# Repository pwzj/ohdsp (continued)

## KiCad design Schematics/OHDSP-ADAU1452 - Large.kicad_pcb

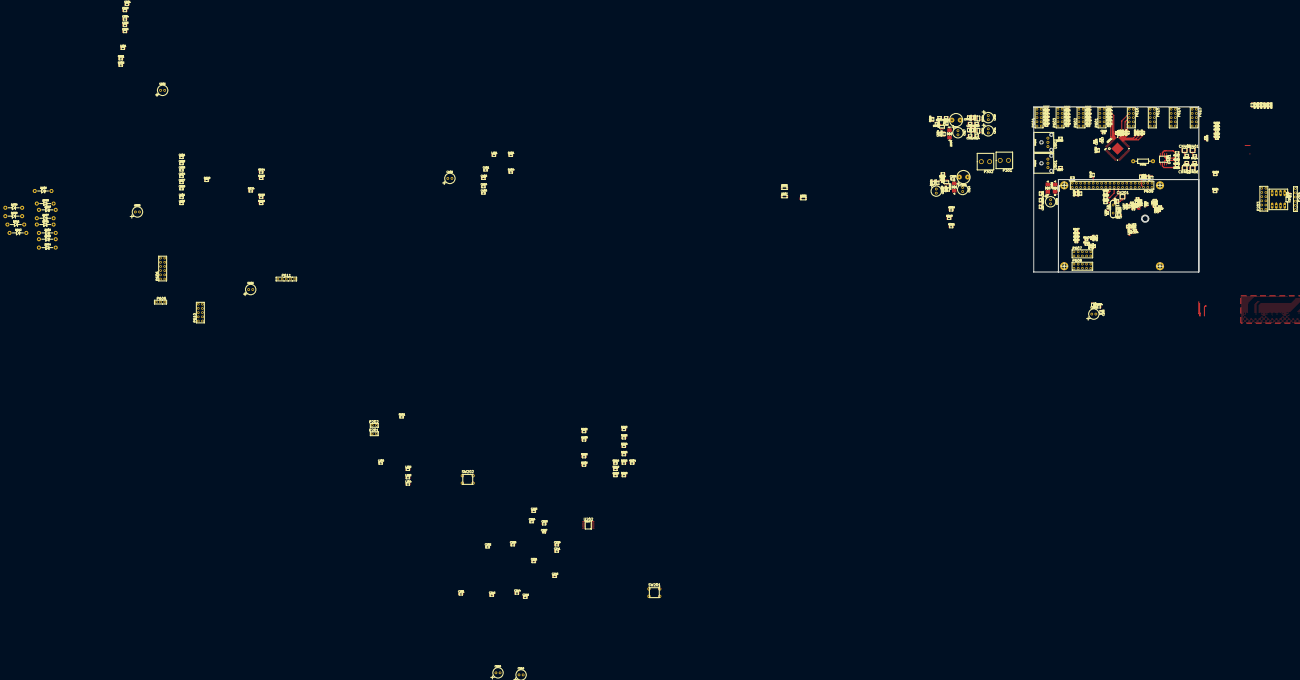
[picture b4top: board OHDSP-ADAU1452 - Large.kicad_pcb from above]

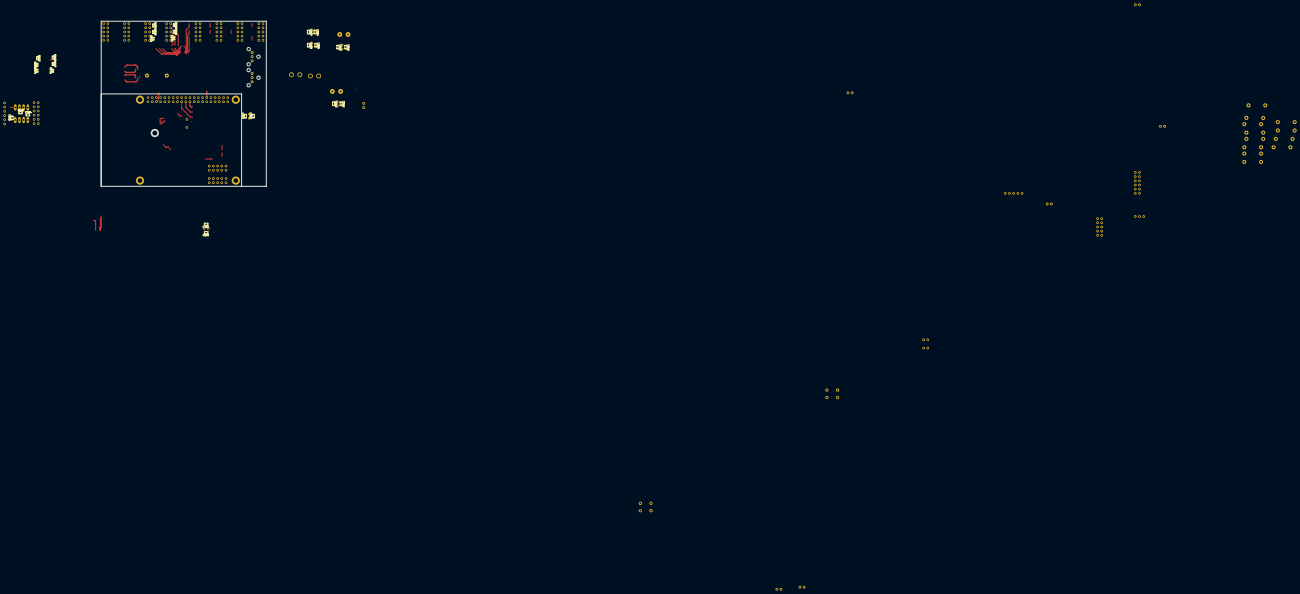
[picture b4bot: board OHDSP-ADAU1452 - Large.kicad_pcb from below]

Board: 2 copper layers, 100.0 x 100.0 mm, 305 parts (27 on the bottom side), 168 nets.

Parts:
C201, C202, C206, C218, C231, C252, C305, C306, C312, C316, C319, C328, C329, C334, C335, C404, C405, C504, C505, C506, C601, C602: 100n; SMD-0805
C203, C214, C224, C239, C245, C307, C401, C501, C607, C608: 100p; SMD-0805
C204, C240, C248, C301, C308, C314, C317, C402, C502, C605, C606: 220u; CAP-TH-D6.3mmP2.5mm
C205, C226, C241, C250, C303, C304, C311, C313, C315, C325, C326, C337, C338, C403, C503, C603, C604: 22u; SMD-0805
C207, C210, C213, C219, C228, C230, C233, C235: 1u; SMD-0603
C208, C211, C215, C220, C227, C229, C232, C234, C236, C242, C251: 100n; SMD-0603
C209, C212, C217, C223: 10n; SMD-0603
C216, C254, C321, C330: 1u; SMD-0805
C221: 5n6; SMD-0603
C222: 150p; SMD-0603
C225: 220u; SMD-0805
C237, C238: 33p; SMD-0603
C309, C310, C331, C507: 10n; SMD-0805
C340, C341: 100u; CAP-TH-D6.3mmP2.5mm
CN201, CN401, CN402, CN405, CN406: COAX; CONN-RF-UFL
D301, D302, D303, D304: SS24T3G; DIODE-SMB
D305, D306, D307: LED; SMD-1206
D601, D602, D603, D604, D605, D606, D607, D608, D609, D610, D611, D612: 1N5818; DIODE-DO-41
L201, L202, L203, L204, L205, L301, L401, L501, L601, L602: 600R@100MHz; SMD-0805
L302: 744772047; PASSIVE-TH-IND-WURTH-5mm
L303: 744772220; PASSIVE-TH-IND-WURTH-5mm
P201, P202: CONN_2x1; CONN_SIL_2
P203, P606: CONN_6X2; CONN_DIL_2X6
P204: CONN_6x1; CONN_SIL_6
P301, P302: CONN_2x1; CONN-SCREW-2WAY-5mm-5.08mm
P303, P304, P305, P306: PIN; MNT_HOLE_2.5mm
P601, P602, P603, P604, P607, P608, P610, P613, P614, P615, P616: CONN_02X05; CONN_DIL_2X5
P605: CONN_3x1; CONN_SIL_3
P609: CONN_02X20; CONN_DIL_2X20
P611: CONN_5x1; CONN_SIL_5
R201, R205, R404: 1k; SMD-0805
R202, R203: 2k2; SMD-0805
R204, R206, R225, R228, R234, R303, R401, R501, R648, R649: 47R; SMD-0805
R207, R208, R209, R210, R213, R214, R604, R605, R606, R607, R608, R609, R610, R611, R612, R613, R614, R615: 0R; SMD-0603
R211, R212, R215, R216, R616, R617, R618, R619, R620, R621, R622, R623, R624, R625, R626, R627, R662, R663, R664, R665, R666, R667, R668, R669, R670, R671, R672, R673: N/F; SMD-0603
R217: 4k3; SMD-0805
R218, R221, R308, R503, R628, R629, R630, R631, R632, R633, R634, R641, R643, R644, R645, R646, R647: 0R; SMD-0805
R219: 12k; SMD-0805
R220: 3k3; SMD-0805
R222, R229, R230, R414, R415, R418, R419, R601, R602, R603, R674: N/F; SMD-0805
R223: 3k; SMD-0805
R224: 3k6; SMD-0805
R226, R301, R302, R313: 100k; SMD-0805
R227: 100R; SMD-0805
R231, R232, R307, R314, R502: 10k; SMD-0805
R304: 47k; SMD-0805
R305: 97k6; SMD-0805
R306: 39k; SMD-0805
R309, R310, R311: 470R; SMD-0805
R402: 75R; TH-RES-0W25
R406, R407, R408, R409: 27R; SMD-0805
R635, R636, R637, R638, R639, R640: 4k7; SMD-0805
R650, R651, R652, R653, R654, R655, R656, R657, R658, R659, R660, R661: 27R; SMD-0603
SW201, SW202: SWITCH; SW_TACT_TH
U201: ADAU1452WBCPZ; IC-LFCSP72-HANDFIT
U202: ADM13307-5ARZ; IC_SOIC_8
U203: 25AA1024; IC_DIP_8
U301, U302: IC-REG-XRP7659ISTR-F; IC-SOT23-6
U304, U305: IC-REG-XC6210B332MR; IC-SOT25
U401: NB3L553; IC_SOIC_8
U501: IC-SPDIF-RX-OPTO; IC_SPDIF_OPTO
U502: IC-SPDIF-TX-OPTO; IC_SPDIF_OPTO
X201: 24M576; XTAL_HC49_TH

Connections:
+5V: D301.1, L602.1, P301.1, R641.2
/ADAU1452/ADAU_SPDIF_RX: C507.1, U201.4
/ADAU1452/ADAU_SPDIF_TX: R503.1, U201.5
/ADAU1452/ADCIN_BCLK0: R605.2, R620.2, U201.58
/ADAU1452/ADCIN_BCLK1: R608.2, R621.2, U201.61
/ADAU1452/ADCIN_BCLK2: R611.2, R622.2, U201.66
/ADAU1452/ADCIN_BCLK3: R602.2, R614.2, R623.2, U201.69
/ADAU1452/ADCIN_LRCLK0: R604.2, R624.2, U201.57
/ADAU1452/ADCIN_LRCLK1: R607.2, R625.2, U201.60
/ADAU1452/ADCIN_LRCLK2: R610.2, R626.2, U201.65
/ADAU1452/ADCIN_LRCLK3: R601.2, R613.2, R627.2, U201.68
/ADAU1452/ADCIN_SDATA0: R606.2, R616.2, U201.59
/ADAU1452/ADCIN_SDATA1: R609.2, R617.2, U201.62
/ADAU1452/ADCIN_SDATA2: R612.2, R618.2, U201.67
/ADAU1452/ADCIN_SDATA3: R603.2, R615.2, R619.2, U201.70
/ADAU1452/AVDD: C248.1, C250.1, C251.1, L205.2, R234.1, U201.7
/ADAU1452/DACOUT_BCLK0: R651.1, U201.40
/ADAU1452/DACOUT_BCLK1: R654.1, U201.43
/ADAU1452/DACOUT_BCLK2: R657.1, U201.48
/ADAU1452/DACOUT_BCLK3: R660.1, U201.51
/ADAU1452/DACOUT_LRCLK0: R650.1, U201.39
/ADAU1452/DACOUT_LRCLK1: R653.1, U201.42
/ADAU1452/DACOUT_LRCLK2: R656.1, U201.47
/ADAU1452/DACOUT_LRCLK3: R659.1, U201.50
/ADAU1452/DACOUT_SDATA0: R652.1, U201.41
/ADAU1452/DACOUT_SDATA1: R655.1, U201.44
/ADAU1452/DACOUT_SDATA2: R658.1, U201.49
/ADAU1452/DACOUT_SDATA3: R661.1, U201.52
/ADAU1452/DVDD: C204.1, C205.1, C206.1, C207.1, C208.1, C209.1, C210.1, C211.1, C212.1, C213.1, C215.1, C217.1, C219.1, C220.1, C223.1, L201.2, R204.1, U201.20, U201.35, U201.53, U201.71
/ADAU1452/EE_SCK: P203.6, P204.3, U203.6
/ADAU1452/EE_SI: P203.8, P204.4, U203.5
/ADAU1452/EE_SO: P203.4, P204.2, U203.2
/ADAU1452/EE_~CS: P203.10, P204.5, R231.2, U203.1
/ADAU1452/I2C_SCL: P605.1, P607.5, P608.5, P610.1, R202.2, R210.1, R630.1
/ADAU1452/I2C_SDA: P605.2, P607.7, P608.7, P610.3, R203.2, R208.1, R629.1
/ADAU1452/IOVDD: C225.1, C226.1, C227.1, C228.1, C229.1, C230.1, C232.1, C233.1, C234.1, C235.1, C236.1, L203.2, R211.1, R212.1, R225.1, U201.2, U201.18, U201.38, U201.56
/ADAU1452/MCLK: R402.2, U201.23
/ADAU1452/M_MISO: P203.3, U201.29
/ADAU1452/M_MOSI: P203.7, U201.27
/ADAU1452/M_SCLK: P203.5, U201.28
/ADAU1452/M_SS: P203.9, U201.26
/ADAU1452/PVDD: C221.1, C222.1, C240.1, C241.1, C242.1, L204.2, R228.1, U201.15
/ADAU1452/RESET: R226.1, U201.24, U202.6
/ADAU1452/SELFBOOT: C202.1, P201.1, R201.2, SW201.1, U201.34
/ADAU1452/SPI_MISO: P610.5, P611.3, R207.1, R632.1
/ADAU1452/SPI_MOSI: P610.8, P611.1, R213.1, R631.1
/ADAU1452/SPI_SCLK: P610.7, P611.2, R209.1, R633.1
/ADAU1452/SPI_~CS: P610.9, P611.4, R214.1, R644.2
/ADAU1452/XTALIN: C237.1, R229.1, R230.1, U201.21, X201.1
/ADAU1452/XTALOUT: R227.1, U201.22
/ClockFanout/MCLKA1: R402.1, U401.5
/ClockFanout/MCLKB1: R406.2, U401.2
/ClockFanout/MCLKB2: R407.2, U401.3
/ClockFanout/MCLKB3: R408.2, U401.6
/ClockFanout/MCLKB4: R409.2, U401.7
/ClockFanout/MCLKC1: CN401.1, R406.1, R414.2
/ClockFanout/MCLKC2: CN405.1, R407.1, R418.2
/ClockFanout/MCLKC3: CN402.1, R408.1, R415.2
/ClockFanout/MCLKC4: CN406.1, R409.1, R419.2
/Connectors/AUXADCIN_1: D601.1, D602.2, R635.2, U201.8
/Connectors/AUXADCIN_2: D603.1, D604.2, R636.2, U201.9
/Connectors/AUXADCIN_3: D605.1, D606.2, R637.2, U201.10
/Connectors/AUXADCIN_4: D607.1, D608.2, R638.2, U201.11
/Connectors/AUXADCIN_5: D609.1, D610.2, R639.2, U201.12
/Connectors/AUXADCIN_6: D611.1, D612.2, R640.2, U201.13
/Connectors/RPI_BCLK: R602.1, R643.2
/Connectors/RPI_LRCLK: R601.1, R634.1
/Connectors/RPI_SDATA_IN: R646.2, R674.2
/Connectors/RPI_SDATA_OUT: R603.1, R647.2
GNDD: C201.2, C202.2, C203.2, C204.2, C205.2, C206.2, C207.2, C208.2, C209.2, C210.2, C211.2, C212.2, C213.2, C214.2, C215.2, C216.2, C217.2, C218.2, C219.2, C220.2, C223.2, C224.2, C225.2, C226.2, C227.2, C228.2, C229.2, C230.2, C231.2, C232.2, C233.2, C234.2, C235.2, C236.2, C237.2, C238.2, C239.2, C240.2, C241.2, C242.2, C245.2, C248.2, C250.2, C251.2, C252.2, C254.2, C301.2, C303.1, C304.1, C305.1, C306.1, C307.2, C308.2, C311.1, C312.1, C313.2, C314.2, C315.2, C316.2, C317.2, C319.2, C321.2, C325.2, C326.2, C328.2, C329.2, C330.2, C331.2, C334.2, C335.2, C337.2, C338.2, C340.2, C341.2, C401.2, C402.2, C403.2, C404.2, C405.2, C501.2, C502.2, C503.2, C504.2, C505.2, C506.2, C601.2, C602.2, C603.2, C604.2, C605.2, C606.2, C607.2, C608.2, CN201.2, CN401.2, CN402.2, CN405.2, CN406.2, D303.1, D304.1, D305.2, D306.2, D307.2, D602.1, D604.1, D606.1, D608.1, D610.1, D612.1, P201.2, P203.11, P203.12, P204.6, P301.2, P302.2, P303.1, P304.1, P305.1, P306.1, P601.1, P601.2, P601.3, P601.5, P601.7, P601.9, P601.10, P602.1, P602.2, P602.3, P602.5, P602.7, P602.9, P602.10, P603.1, P603.2, P603.3, P603.5, P603.7, P603.9, P603.10, P604.1, P604.2, P604.3, P604.5, P604.7, P604.9, P604.10, P605.3, P606.1, P606.3, P606.5, P606.7, P606.9, P606.11, P607.1, P607.3, P607.4, P607.8, P607.9, P607.10, P608.1, P608.3, P608.4, P608.8, P608.9, P608.10, P609.6, P609.9, P609.14, P609.20, P609.25, P609.30, P609.34, P609.39, P610.10, P611.5, P613.1, P613.2, P613.3, P613.5, P613.7, P613.9, P613.10, P614.1, P614.2, P614.3, P614.5, P614.7, P614.9, P614.10, P615.1, P615.2, P615.3, P615.5, P615.7, P615.9, P615.10, P616.1, P616.2, P616.3, P616.5, P616.7, P616.9, P616.10, R205.2, R215.1, R216.1, R221.1, R222.1, R223.1, R224.1, R226.2, R229.2, R305.2, R308.2, R414.1, R415.1, R418.1, R419.1, R616.1, R617.1, R618.1, R619.1, R620.1, R621.1, R622.1, R623.1, R624.1, R625.1, R626.1, R627.1, R662.1, R663.1, R664.1, R665.1, R666.1, R667.1, R668.1, R669.1, R670.1, R671.1, R672.1, R673.1, SW201.2, SW202.2, U201.1, U201.6, U201.14, U201.17, U201.19, U201.25, U201.36, U201.37, U201.54, U201.55, U201.72, U201.EP1, U202.4, U203.4, U301.2, U302.2, U304.2, U305.2, U401.4, U501.2, U502.3
unnamed: C203.1, R204.2
unnamed: C214.1, R206.2
unnamed: C216.1, C218.1, L202.2, R206.1, U202.8
unnamed: C221.2, R217.1
unnamed: C222.2, R217.2, U201.16
unnamed: C224.1, R225.2
unnamed: C231.1, SW202.1, U202.7
unnamed: C238.1, R227.2, X201.2
unnamed: C239.1, R228.2
unnamed: C245.1, R234.2
unnamed: C252.1, C254.1, P203.2, P204.1, R231.1, R232.1, U203.8
unnamed: C307.1, R303.2
unnamed: C309.1, U301.1
unnamed: C309.2, D303.2, L302.1, U301.6
unnamed: C310.1, U302.1
unnamed: C310.2, D304.2, L303.1, U302.6
unnamed: C315.1, C317.1, C319.1, C325.1, C326.1, C328.1, C329.1, L303.2, R306.1, R313.1, R314.1, U304.1, U305.1
unnamed: C321.1, R301.1, U301.4
unnamed: C330.1, R313.2, U304.3
unnamed: C331.1, R314.2, U305.3
unnamed: C401.1, R401.2
unnamed: C402.1, C403.1, C404.1, C405.1, L401.2, R401.1, R404.2, U401.1
unnamed: C501.1, R501.2
unnamed: C502.1, C503.1, C504.1, C505.1, C506.1, L501.2, R501.1, R502.1, U501.1, U502.2
unnamed: C507.2, R502.2, U501.3
unnamed: C601.1, C603.1, C605.1, L601.2, P607.2, P608.2, R648.2
unnamed: C602.1, C604.1, C606.1, L602.2, P607.6, P608.6, R649.2
unnamed: C607.1, R648.1
unnamed: C608.1, R649.1
unnamed: CN201.1, R230.2
unnamed: D301.2, D302.2, L301.1
unnamed: D302.1, P302.1
unnamed: D305.1, R309.2
unnamed: D306.1, R310.2
unnamed: D307.1, R311.2
unnamed: P202.2, R205.1
unnamed: P601.4, R604.1
unnamed: P601.6, R605.1
unnamed: P601.8, R606.1
unnamed: P602.4, R607.1
unnamed: P602.6, R608.1
unnamed: P602.8, R609.1
unnamed: P603.4, R610.1
unnamed: P603.6, R611.1
unnamed: P603.8, R612.1
unnamed: P604.4, R613.1
unnamed: P604.6, R614.1
unnamed: P604.8, R615.1
unnamed: P606.2, R635.1
unnamed: P606.4, R636.1
unnamed: P606.6, R637.1
unnamed: P606.8, R638.1
unnamed: P606.10, R639.1
unnamed: P606.12, R640.1
unnamed: P609.1, R628.2
unnamed: P609.2, P609.4, R641.1
unnamed: P609.3, R629.2
unnamed: P609.5, R630.2
unnamed: P609.12, R643.1
unnamed: P609.19, R631.2
unnamed: P609.21, R632.2
unnamed: P609.23, R633.2
unnamed: P609.24, R644.1
unnamed: P609.26, R645.1
unnamed: P609.35, R634.2
unnamed: P609.38, R646.1
unnamed: P609.40, R647.1
unnamed: P613.4, R650.2, R670.2
unnamed: P613.6, R651.2, R666.2
unnamed: P613.8, R652.2, R662.2
unnamed: P614.4, R653.2, R671.2
unnamed: P614.6, R654.2, R667.2
unnamed: P614.8, R655.2, R663.2
unnamed: P615.4, R656.2, R672.2
unnamed: P615.6, R657.2, R668.2
unnamed: P615.8, R658.2, R664.2
unnamed: P616.4, R659.2, R673.2
unnamed: P616.6, R660.2, R669.2
unnamed: P616.8, R661.2, R665.2, R674.1
unnamed: R207.2, R208.2, U201.30
unnamed: R209.2, R210.2, U201.31
unnamed: R211.2, R214.2, R216.2, U201.33
unnamed: R212.2, R213.2, R215.2, U201.32
unnamed: R218.2, R222.2, U202.1
unnamed: R219.2, R223.2, U202.2
unnamed: R220.2, R224.2, U202.3
unnamed: R221.2, U201.3
unnamed: R232.2, U203.3
unnamed: R302.1, U302.4
unnamed: R304.2, R305.1, U301.3
unnamed: R306.2, R307.1, U302.3
unnamed: R307.2, R308.1
unnamed: R404.1, U401.8
unnamed: R503.2, U502.1
VAA: C334.1, C337.1, C340.1, L204.1, L205.1, R219.1, R301.2, R310.1, U304.5
VCC: C301.1, C303.2, C304.2, C305.2, C306.2, C308.1, C311.2, C312.2, L301.2, R302.2, R303.1, U301.5, U302.5
VDD: C313.1, C314.1, C316.1, L201.1, L302.2, R220.1, R304.1, R309.1
VPP: C201.1, C335.1, C338.1, C341.1, D601.2, D603.2, D605.2, D607.2, D609.2, D611.2, L202.1, L203.1, L401.1, L501.1, L601.1, P203.1, R201.1, R202.1, R203.1, R218.1, R311.1, U305.5

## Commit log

2015-02-24 Initial Commit
    Initial Commit to master containing KiCad Libraries
2015-02-24 Minor update
2015-02-24 Initial commit in ADAU1452
    Initial commit in ADAU1452, contains work in progress PCB layout and
    schematics. Schematics need reviewing.
2015-02-25 Schematic and PCB changes
    Changed and corrected some footprints, removed capacitors, updated
    documentation to change 1v5 SMPS to 1v2. Have not removed 1v2 LDO from
    schematic yet.
2015-02-25 Remove 1v2 LDO
    Remove 1v2 LDO, not really needed...
2015-02-25 Minor update
    Minor update
2015-02-25 Remove .bak files
2015-02-25 R305 value change for 1v2
    R305 value change for 1v2 from 1v5 value
2015-02-26 Modifiy LFCSP72 to allow for attempted hand soldering...
    Modifiy LFCSP72 to allow for attempted hand soldering.
2015-02-26 Change ADAU1452 footprint, minor PCB changes
2015-02-26 Add 5mmx7mm crystal oscillator footprint for hand fit
    Add 5mmx7mm crystal oscillator footprint for hand fit
2015-02-26 Revert "Add 5mmx7mm crystal oscillator footprint for hand fit"
    This reverts commit a0ed6c03b1596703282a627aa3711e6da4f52fba.
2015-02-26 Revert "Revert "Add 5mmx7mm crystal oscillator footprint for hand fit""
    This reverts commit fe1a51017ccefdd16d0037da8ca0ddc103b71dd7.
2015-02-26 Update git ignore file
2015-02-26 Git ignore...
2015-02-26 Git ignore annoying me now...
2015-02-26 Removed gitignore...
2015-02-26 Rationalise the clock and clock fan-out schematics.
    Rationalise the clock and clock fan-out schematics.
    Removed one clock fan out buffer, still have 4 master audio clock
    outputs. Also removed local crytsal oscialltor, a low jitter crystal
    should perform as well, ADAU1452 has internal "dejittering" anyway.
2015-02-26 PCB work
2015-02-26 Added large pcb layout
    Added large pcb layout. Believe kicad expects 1 pcb per project so it
    has created an extra .pro file which should be ignored. This is a bit of
    a hack but it seems to work for now...
2015-02-26 Revert "Added large pcb layout"
    This reverts commit cdcde476aac2cbdae67bb5f0de8b4259defc0766.
2015-02-26 Add large pcb layout
    Added large pcb layout, kicad created additional .pro file which can be
    ignored, a bit of a hack but it works for the moment...
2015-02-26 Going 4 layer on smaller PCB
    Going 4 layer on smaller PCB
2015-02-26 Revert "Going 4 layer on smaller PCB"
    This reverts commit d1ec277a0becb058c7967dba94e28e7f31b1a00f.
2015-02-26 Revert "Revert "Going 4 layer on smaller PCB""
    This reverts commit a2928be1b12072271fc86fb10f3c648b88b658e1.
2015-02-26 Going 4 layer on small PCB
    Going 4 layer on small PCB
2015-02-27 PCB work
    More pcb work, some footprint changes, previous commit also had some
    minor footprint changes and 0R resistors added...
2015-02-28 PCB work, footprint changes
2015-02-28 Footprint changes
    Footprint changes
2015-03-02 PCB changes, minor schematic changes
    Removed switch on selfboot pin, as it has a jumper anyway... Removed
    SPI/I2C jumper for selfboot as sticking with serial EEPROM. Changed some
    component footprints (R207 to R216 0603 to 0805).
2015-03-03 PCB work, removed a cap
2015-03-03 Added SMD tact switch foorprint
    Added SMD tact switch foorprint
2015-03-03 PCB Work, change reset switch to SMD
2015-03-04 PCB Work, minor schematic changes
    Removed cap and LED, changed one net label
2015-03-04 PCB work, remove 5v from I2C headers
2015-03-04 PCB work, added manual reset to Pi header
2015-03-04 PCB work
    Also playing with via sizes...
2015-03-07 PCB work, removed pointless connector
2015-03-10 PCB work, extra Pi GPIO to external connectors
    PCB work, extra Pi GPIO to external connectors
2015-03-10 PCB work, Running Electrical Rule Check
    PCB work, Running Electrical Rule Check:
    Added no connects to schematics, added missing pull up on EEPROM, remove
    USB_CLK/USB_RESET label on USB/I2C header and added NC. Minor change on
    Pi connectors.
    Removed old large PCB file.
2015-03-10 PCB work, ADAU reset changes
    Added caps to reset lines
2015-03-11 PCB work, SPDIF filter caps changed
2015-03-11 PCB work
    Corrected trace width notes, need to change PCB traces to match
2015-03-12 Add new ADC and DAC
    Add WM8501 DAC and WM8783 ADC and SOIC 14 footprint
2015-03-12 Adding Simple ADC and DAC option
    Adding Simple ADC and DAC option
    Will see if it fits in the remaining space for a 10cmx10cm PCB, have to
    pay for the space for anysize up to 10x10cm to may as well use it.
2015-03-12 Adding ADC/DAC
2015-03-12 Add 5mm PP/MKP cap footprint
2015-03-12 Adding DAC/ADC
2015-03-12 PCB work, added DAC/ADC
2015-03-13 PCB work
    Need to finish sorting SPI lines, currently a mix of 0.25mm and 0.2mm on
    the same traces...
2015-03-25 Adding ADAU1701 version
    Because its easier...
2015-03-26 Add I2C EEPROM
2015-03-26 Add 2x10 connector
2015-03-26 Correct NCP700B pin out
2015-03-26 Add transistors and SOT23
2015-03-27 Modify NPN/PNP transistors
2015-03-27 Add NC7SZU04M5X and SOT23-5
2015-03-27 Add test points
2015-03-30 WIP PSU changes
2015-03-30 Add LT1374, inductor and SMC diode
2015-03-30 WIP
    Removed Slave SPI as only really need I2C
    Should free up some space on the board.
    May look to change U.fl to SMA
2015-03-31 Add 4 pin DIL crystal oscillator
2015-04-01 Add 2x5 DIL box header footprint
2015-04-04 Add ADM811 reset generator and SOT143
2015-04-06 Change reset chip to ADM811
2015-04-08 Add 2x10 2.54mm box header footprint
2015-04-08 Change to box headers
2015-04-11 Playing with different connectors....
2015-05-24 WIP
    Add master audio clock to I2S headers.
2015-05-29 WIP
    Remove unneeded parts around SPI EEPROM
2015-05-29 WIP
    Simplify PSU
2015-06-04 Add AD1937 CODEC- No footprint
    Added AD1937 CODEC, need to add LQFP64 10x10 footprint
2015-06-05 Add LQFP64 Footprint
2015-06-10 Add ATmega32U4 and QFP44
